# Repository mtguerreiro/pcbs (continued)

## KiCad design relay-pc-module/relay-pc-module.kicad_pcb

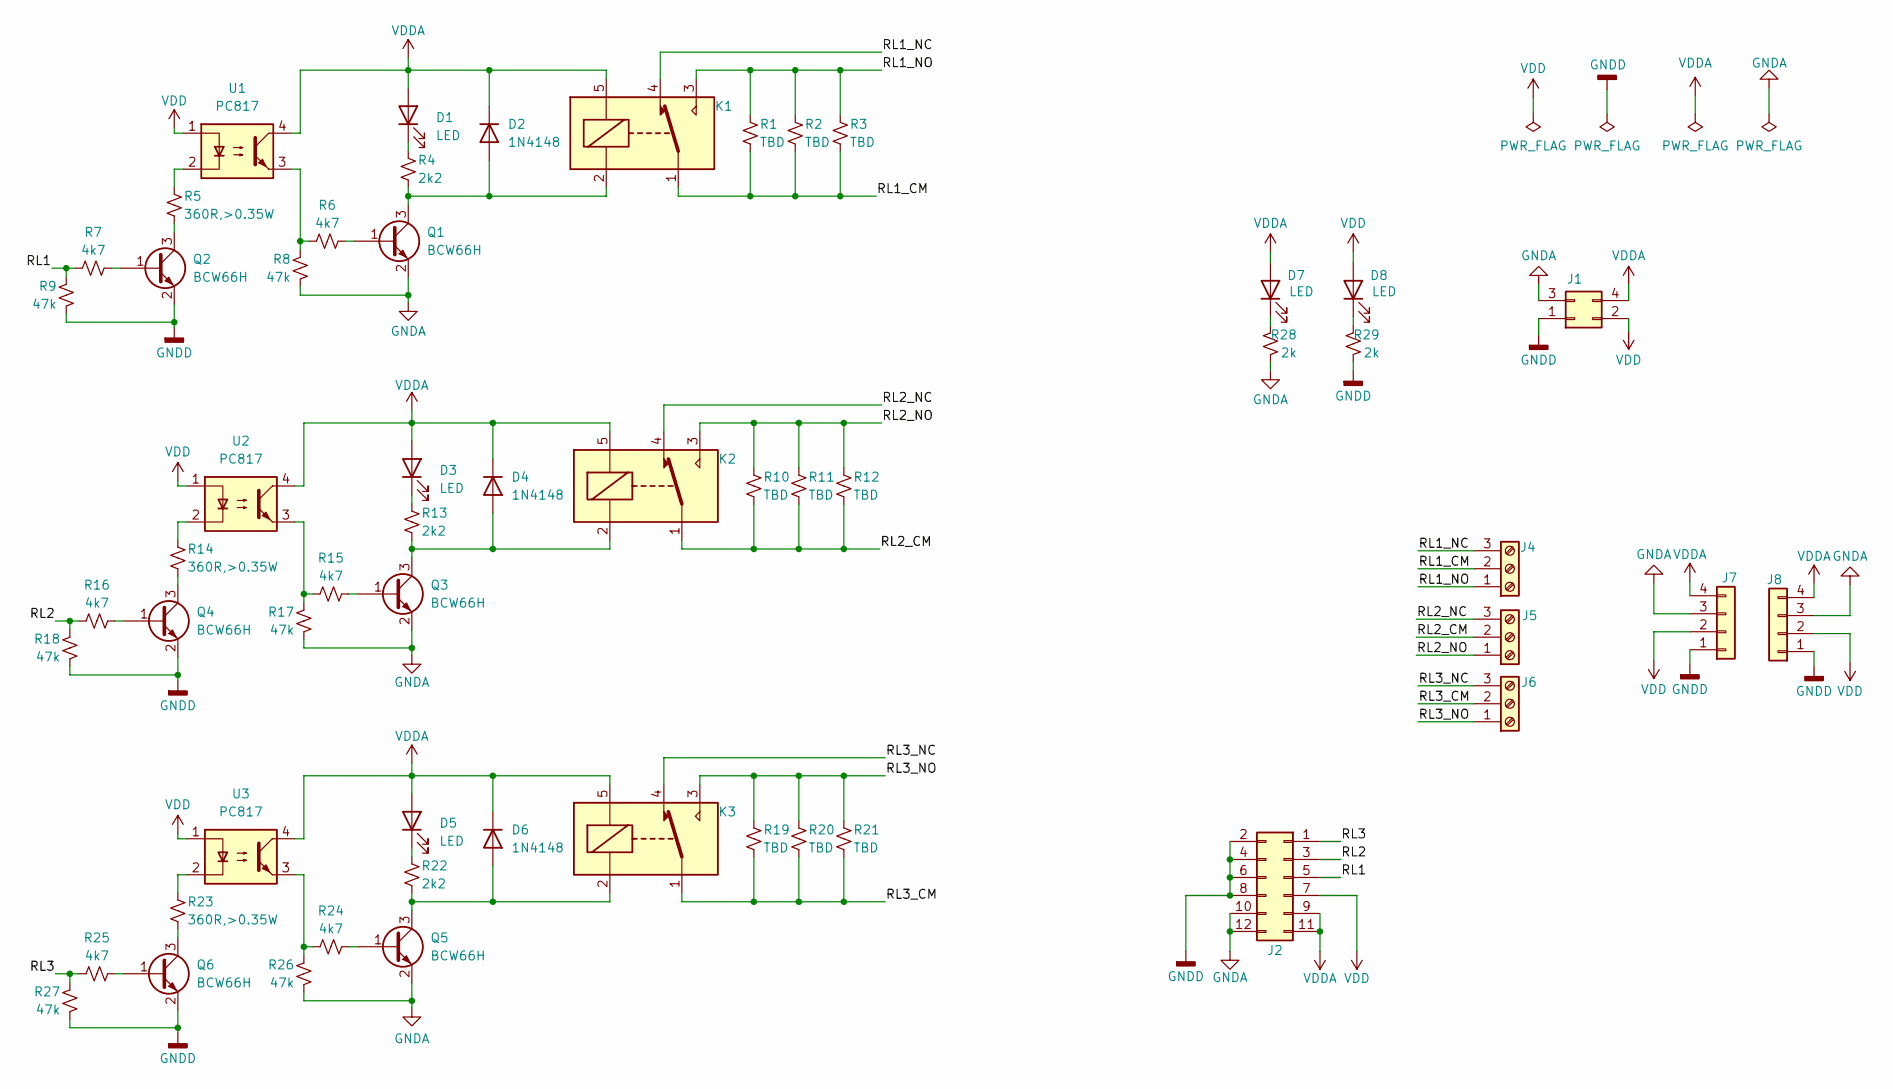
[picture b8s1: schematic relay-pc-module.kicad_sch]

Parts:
D1, D3, D5, D7, D8: LED; LED_0805_2012Metric_Pad1.15x1.40mm_HandSolder
D2, D4, D6: 1N4148; D_SOD-123
J1: Conn_02x02_Odd_Even; PinHeader_2x02_P2.54mm_Vertical
J2: Conn_02x06_Odd_Even; PinHeader_2x06_P2.54mm_Horizontal
J4, J5, J6: Screw_Terminal_01x03; TerminalBlock_Phoenix_MKDS-1,5-3-5.08_1x03_P5.08mm_Horizont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
J7, J8: Conn_01x04; PinHeader_1x04_P2.54mm_Vertical
K1, K2, K3: SANYOU_SRD_Form_C; Relay_SPDT_SANYOU_SRD_Series_Form_C
Q1, Q2, Q3, Q4, Q5, Q6: BCW66H; SOT-23W
R1, R2, R3, R10, R11, R12, R19, R20, R21: TBD; R_Axial_DIN0617_L17.0mm_D6.0mm_P5.08mm_Vertical
R4, R13, R22: 2k2; R_0805_2012Metric_Pad1.20x1.40mm_HandSolder
R5, R14, R23: 360R,>0.35W; R_0805_2012Metric_Pad1.20x1.40mm_HandSolder
R6, R7, R15, R16, R24, R25: 4k7; R_0805_2012Metric_Pad1.20x1.40mm_HandSolder
R8, R9, R17, R18, R26, R27: 47k; R_0805_2012Metric_Pad1.20x1.40mm_HandSolder
R28, R29: 2k; R_0805_2012Metric_Pad1.20x1.40mm_HandSolder
U1, U2, U3: PC817; DIP-4_W8.89mm_SMDSocket_LongPads

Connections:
/RL1: J2.5, R7.1, R9.2
/RL1_CM: J4.2, K1.1, R1.2, R2.2, R3.2
/RL1_NC: J4.3, K1.4
/RL1_NO: J4.1, K1.3, R1.1, R2.1, R3.1
/RL2: J2.3, R16.1, R18.2
/RL2_CM: J5.2, K2.1, R10.2, R11.2, R12.2
/RL2_NC: J5.3, K2.4
/RL2_NO: J5.1, K2.3, R10.1, R11.1, R12.1
/RL3: J2.1, R25.1, R27.2
/RL3_CM: J6.2, K3.1, R19.2, R20.2, R21.2
/RL3_NC: J6.3, K3.4
/RL3_NO: J6.1, K3.3, R19.1, R20.1, R21.1
GNDA: J1.3, J2.10, J2.12, J7.3, J8.3, Q1.2 (E), Q3.2 (E), Q5.2 (E), R8.1, R17.1, R26.1, R28.1
GNDD: J1.1, J2.2, J2.4, J2.6, J2.8, J7.1, J8.1, Q2.2 (E), Q4.2 (E), Q6.2 (E), R9.1, R18.1, R27.1, R29.1
unnamed: D1.1 (K), R4.2
unnamed: D2.2 (A), K1.2, Q1.3 (C), R4.1
unnamed: D3.1 (K), R13.2
unnamed: D4.2 (A), K2.2, Q3.3 (C), R13.1
unnamed: D5.1 (K), R22.2
unnamed: D6.2 (A), K3.2, Q5.3 (C), R22.1
unnamed: D7.1 (K), R28.2
unnamed: D8.1 (K), R29.2
unnamed: Q1.1 (B), R6.2
unnamed: Q2.1 (B), R7.2
unnamed: Q2.3 (C), R5.1
unnamed: Q3.1 (B), R15.2
unnamed: Q4.1 (B), R16.2
unnamed: Q4.3 (C), R14.1
unnamed: Q5.1 (B), R24.2
unnamed: Q6.1 (B), R25.2
unnamed: Q6.3 (C), R23.1
unnamed: R5.2, U1.2
unnamed: R6.1, R8.2, U1.3
unnamed: R14.2, U2.2
unnamed: R15.1, R17.2, U2.3
unnamed: R23.2, U3.2
unnamed: R24.1, R26.2, U3.3
VDD: D8.2 (A), J1.2, J2.7, J7.2, J8.2, U1.1, U2.1, U3.1
VDDA: D1.2 (A), D2.1 (K), D3.2 (A), D4.1 (K), D5.2 (A), D6.1 (K), D7.2 (A), J1.4, J2.9, J2.11, J7.4, J8.4, K1.5, K2.5, K3.5, U1.4, U2.4, U3.4

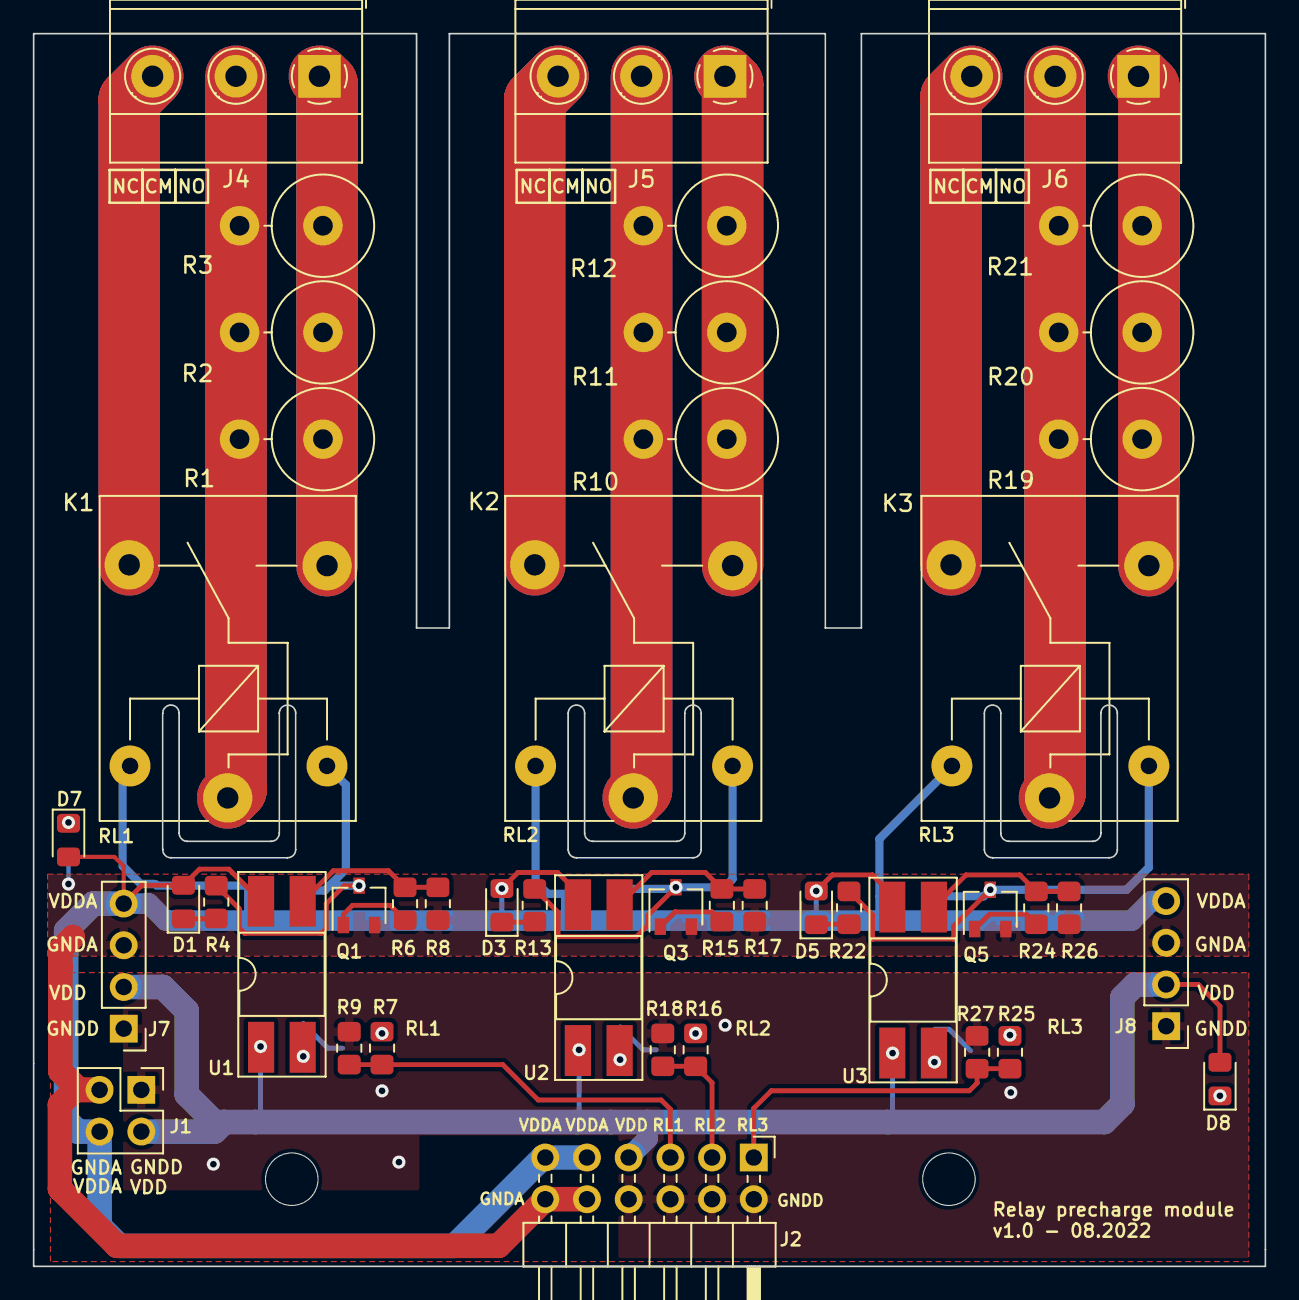
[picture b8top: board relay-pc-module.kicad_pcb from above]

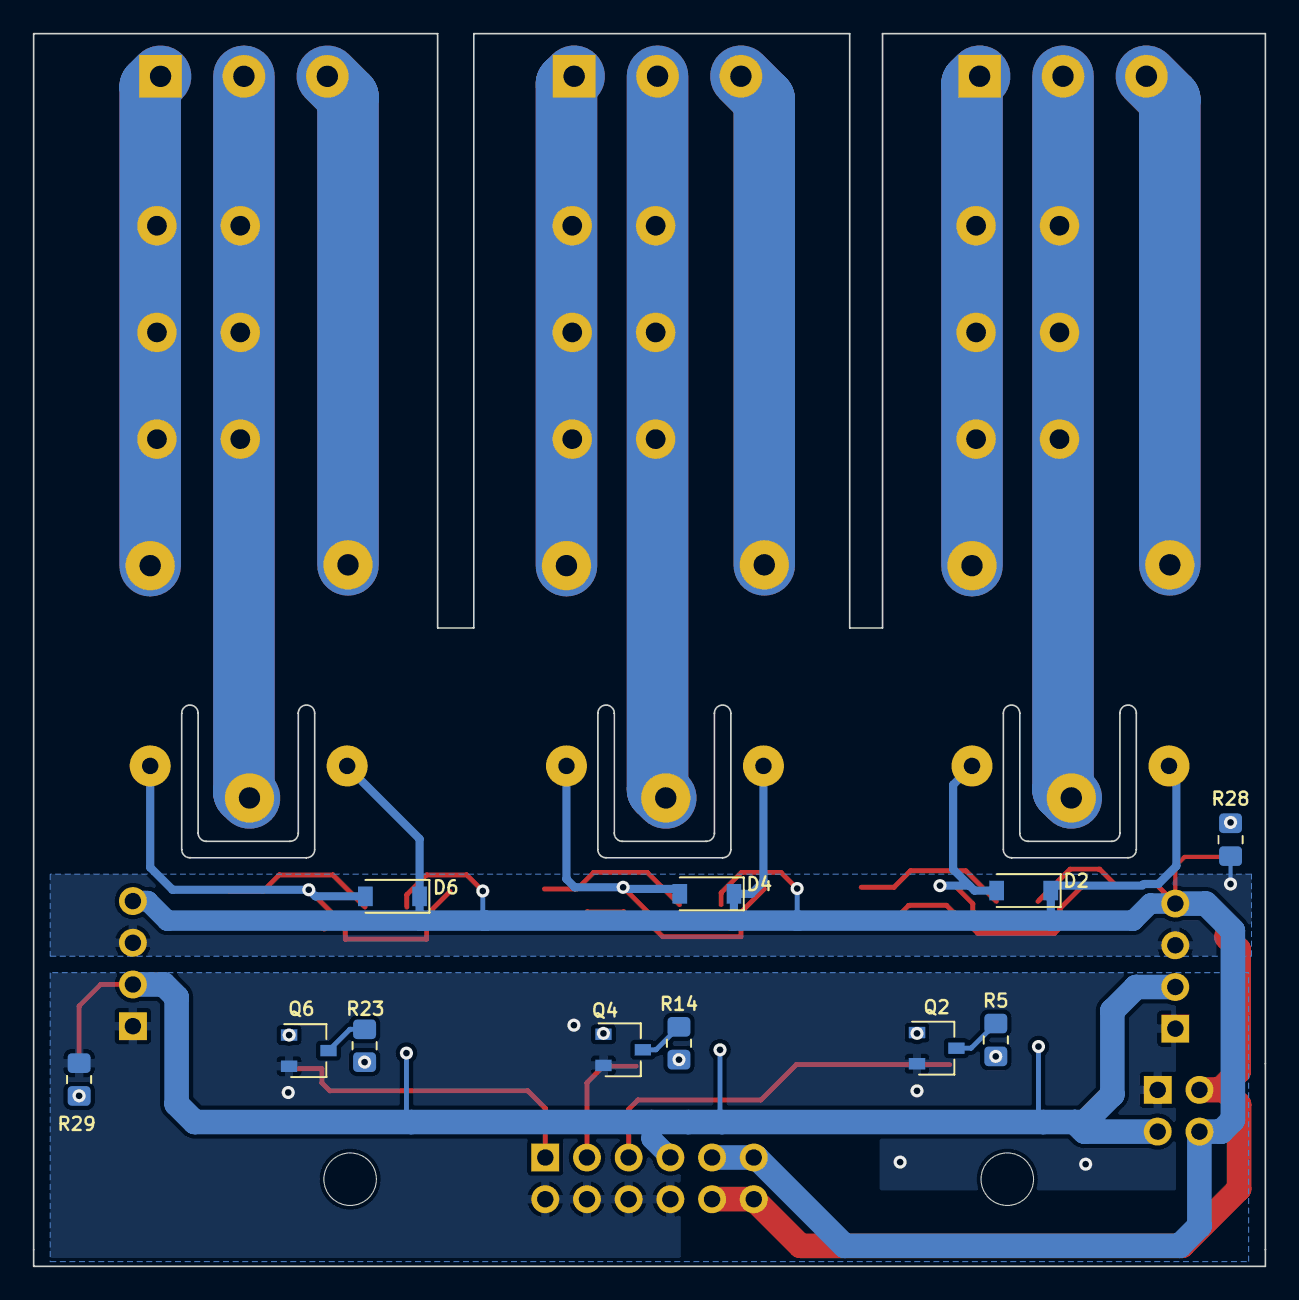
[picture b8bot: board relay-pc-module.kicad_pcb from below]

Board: 2 copper layers, 75.0 x 75.1 mm, 56 parts (11 on the bottom side), 39 nets.
